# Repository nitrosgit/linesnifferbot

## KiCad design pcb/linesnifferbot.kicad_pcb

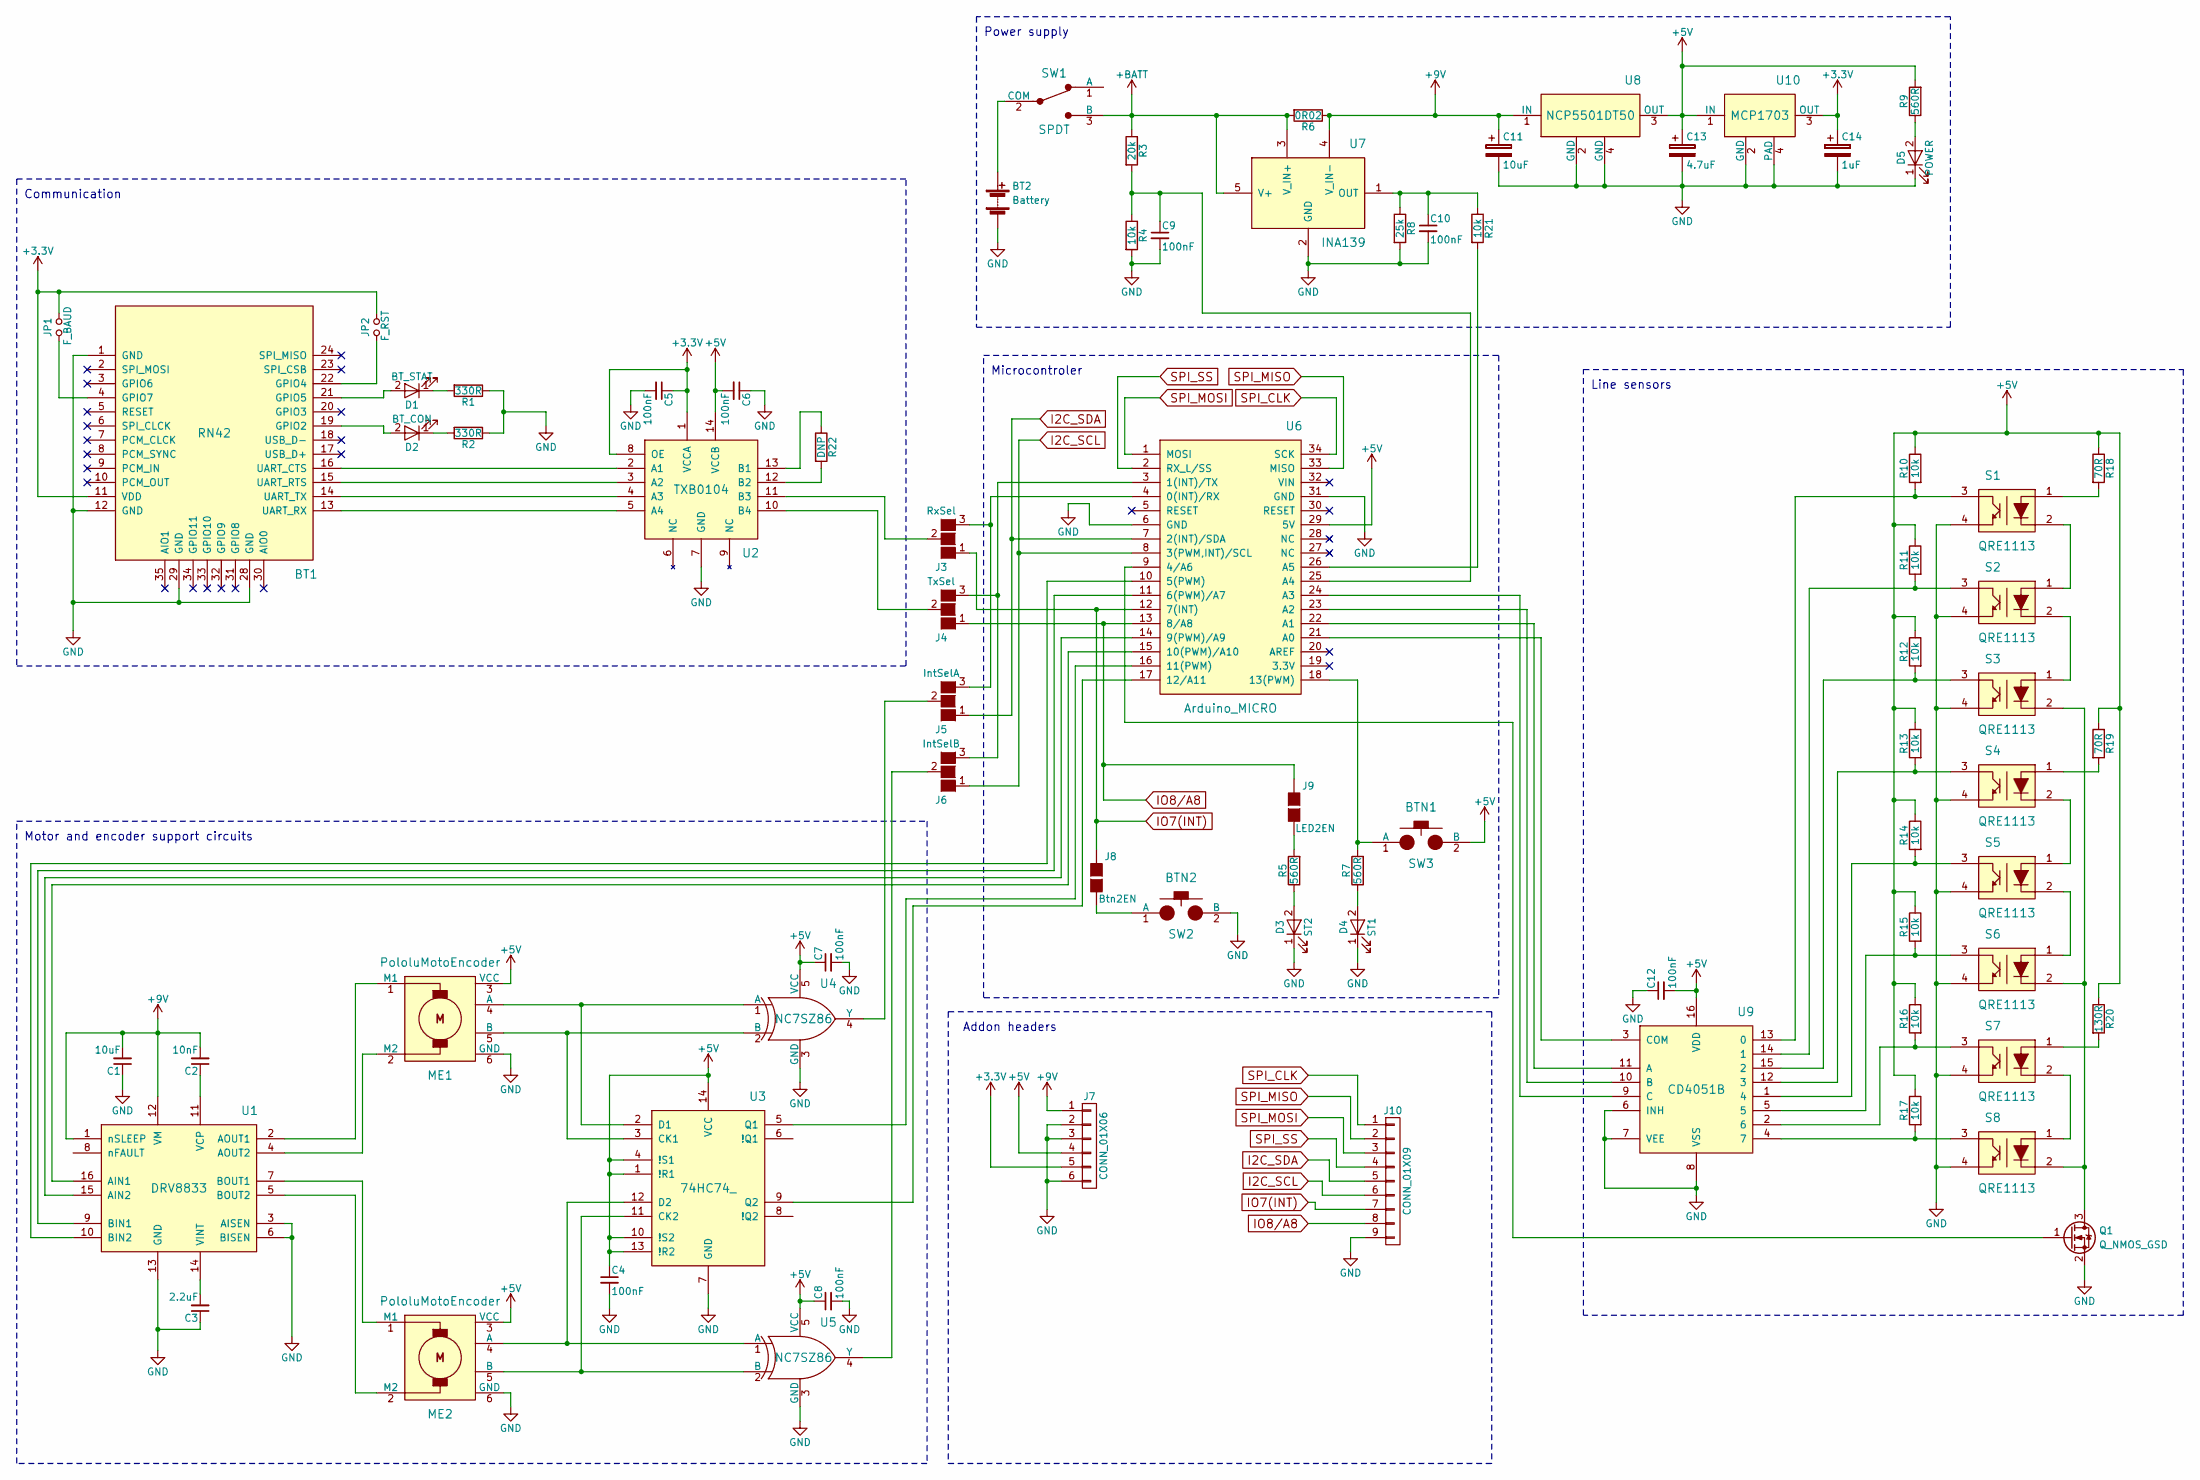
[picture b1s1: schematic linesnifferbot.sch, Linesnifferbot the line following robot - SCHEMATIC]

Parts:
BT1: RN42; RN-42
BT2: Battery; PP3Battery
C1: 10uF; C_1206
C2: 10nF; C_0805
C3: 2.2uF; C_0805
C4, C5, C6, C7, C8, C9, C10, C12: 100nF; C_0805
C11: 10uF; CP_Tantalum_Case-A_EIA-3216-18_Reflow
C13: 4.7uF; CP_Tantalum_Case-A_EIA-3216-18_Reflow
C14: 1uF; CP_Tantalum_Case-A_EIA-3216-18_Reflow
D1: BT_STAT; LED_0805
D2: BT_CON; LED_0805
D3: ST2; LED_0805
D4: ST1; LED_0805
D5: POWER; LED_0805
J3: RxSel; GS3
J4: TxSel; GS3
J5: IntSelA; GS3
J6: IntSelB; GS3
J7: CONN_01X06; Socket_Strip_Straight_1x06_Pitch2.54mm
J8: Btn2EN; GS2
J9: LED2EN; GS2
J10: CONN_01X09; Socket_Strip_Straight_1x09_Pitch2.54mm
JP1: F_BAUD; GS2
JP2: F_RST; GS2
ME1, ME2: PololuMotoEncoder
Q1: Q_NMOS_GSD; SOT-23
R1, R2: 330R; R_0805
R3: 20k; R_0805
R4, R10, R11, R12, R13, R14, R15, R16, R17, R21: 10k; R_0805
R5, R7, R9: 560R; R_0805
R6: 0R02; R_1206
R8: 25k; R_0805
R18, R19: 70R; R_0805
R20: 130R; R_0805
R22: DNP; R_0805
S1, S2, S3, S4, S5, S6, S7, S8: QRE1113; QRE1113GR
SW1: SPDT; SP_ToggleSW
SW2: BTN2; SW_SPST_EVPBF
SW3: BTN1; SW_SPST_EVPBF
U1: DRV8833; TSSOP-16_4.4x5mm_Pitch0.65mm
U2: TXB0104; SOIC-14_3.9x8.7mm_Pitch1.27mm
U3: 74HC74_; SOIC-14_3.9x8.7mm_Pitch1.27mm
U4, U5: NC7SZ86; SOT-23-5
U6: Arduino_MICRO; ArduinoMicro
U7: INA139; SOT-23-5
U8: NCP5501DT50; DPAK3
U9: CD4051B; SOIC-16_3.9x9.9mm_Pitch1.27mm
U10: MCP1703; SOT-223

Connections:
+3V3: BT1.11 (VDD), C5.1, C14.1, J7.5, JP1.2, JP2.2, U2.1 (VCCA), U2.8 (OE), U10.3 (OUT)
+5V: C4.1, C6.2, C7.1, C8.1, C12.2, C13.1, J7.4, ME1.3 (VCC), ME2.3 (VCC), R9.2, R10.1, R11.1, R12.1, R13.1, R14.1, R15.1, R16.1, R17.1, R18.1, R19.1, R20.1, SW3.2 (B), U2.14 (VCCB), U3.1 (!R1), U3.4 (!S1), U3.10 (!S2), U3.13 (!R2), U3.14 (VCC), U4.5 (VCC), U5.5 (VCC), U6.29 (5V), U8.3 (OUT), U9.16 (VDD), U10.1 (IN)
+9V: C1.2, C2.2, C11.1, J7.1, R6.1, U1.1 (nSLEEP), U1.12 (VM), U7.4 (V_IN-), U8.1 (IN)
+BATT: R3.1, R6.2, SW1.3 (B), U7.3 (V_IN+), U7.5 (V+)
GND: BT1.1 (GND), BT1.12 (GND), BT1.28 (GND), BT1.29 (GND), BT2.2 (-), C1.1, C3.1, C4.2, C5.2, C6.1, C7.2, C8.2, C9.2, C10.2, C11.2, C12.1, C13.2, C14.2, D3.1 (K), D4.1 (K), D5.1 (K), J7.2, J7.3, J7.6, J10.9, ME1.6 (GND), ME2.6 (GND), Q1.2 (S), R1.1, R2.1, R4.2, R8.2, S1.4, S2.4, S3.4, S4.4, S5.4, S6.4, S7.4, S8.4, SW2.2 (B), U1.3 (AISEN), U1.6 (BISEN), U1.13 (GND), U2.7 (GND), U3.7 (GND), U4.3 (GND), U5.3 (GND), U6.6 (GND), U6.31 (GND), U7.2 (GND), U8.2 (GND), U8.4 (GND), U9.6 (INH), U9.7 (VEE), U9.8 (VSS), U10.2 (GND), U10.4 (PAD)
I2C_SCL: J6.1 (G1), J10.6, U6.8 (3(PWM,INT)/SCL)
I2C_SDA: J5.1 (G1), J10.5, U6.7 (2(INT)/SDA)
IO7(INT): J3.1 (G1), J8.1 (G1), J10.7, U6.12 (7(INT))
IO8/A8: J4.1 (G1), J9.1 (G1), J10.8, U6.13 (8/A8)
unnamed: BT1.4 (GPIO7), JP1.1
unnamed: BT1.13 (UART_RX), U2.5 (A4)
unnamed: BT1.14 (UART_TX), U2.4 (A3)
unnamed: BT1.15 (UART_RTS), U2.3 (A2)
unnamed: BT1.16 (UART_CTS), U2.2 (A1)
unnamed: BT1.19 (GPIO2), D2.2 (A)
unnamed: BT1.21 (GPIO5), D1.2 (A)
unnamed: BT1.22 (GPIO4), JP2.1
unnamed: BT2.1 (+), SW1.2 (COM)
unnamed: C2.1, U1.11 (VCP)
unnamed: C3.2, U1.14 (VINT)
unnamed: C9.1, R3.2, R4.1, U6.25 (A4)
unnamed: C10.1, R8.1, R21.1, U7.1 (OUT)
unnamed: D1.1 (K), R1.2
unnamed: D2.1 (K), R2.2
unnamed: D3.2 (A), R5.1
unnamed: D4.2 (A), R7.1
unnamed: D5.2 (A), R9.1
unnamed: J3.2 (G2), U2.11 (B3)
unnamed: J3.3 (G3), J5.3 (G3), U6.4 (0(INT)/RX)
unnamed: J4.2 (G2), U2.10 (B4)
unnamed: J4.3 (G3), J6.3 (G3), U6.3 (1(INT)/TX)
unnamed: J5.2 (G2), U4.4 (Y)
unnamed: J6.2 (G2), U5.4 (Y)
unnamed: J8.2 (G2), SW2.1 (A)
unnamed: J9.2 (G2), R5.2
unnamed: ME1.1 (M1), U1.2 (AOUT1)
unnamed: ME1.2 (M2), U1.4 (AOUT2)
unnamed: ME1.4 (A), U3.2 (D1), U4.1 (A)
unnamed: ME1.5 (B), U3.3 (CK1), U4.2 (B)
unnamed: ME2.1 (M1), U1.7 (BOUT1)
unnamed: ME2.2 (M2), U1.5 (BOUT2)
unnamed: ME2.4 (A), U3.12 (D2), U5.1 (A)
unnamed: ME2.5 (B), U3.11 (CK2), U5.2 (B)
unnamed: Q1.1 (G), U6.9 (4/A6)
unnamed: Q1.3 (D), S3.2, S6.2, S8.2
unnamed: R7.2, SW3.1 (A), U6.18 (13(PWM))
unnamed: R10.2, S1.3, U9.13 (0)
unnamed: R11.2, S2.3, U9.14 (1)
unnamed: R12.2, S3.3, U9.15 (2)
unnamed: R13.2, S4.3, U9.12 (3)
unnamed: R14.2, S5.3, U9.1 (4)
unnamed: R15.2, S6.3, U9.5
unnamed: R16.2, S7.3, U9.2 (6)
unnamed: R17.2, S8.3, U9.4 (7)
unnamed: R18.2, S1.1
unnamed: R19.2, S4.1
unnamed: R20.2, S7.1
unnamed: R21.2, U6.26 (A5)
unnamed: R22.1, U2.13 (B1)
unnamed: R22.2, U2.12 (B2)
unnamed: S1.2, S2.1
unnamed: S2.2, S3.1
unnamed: S4.2, S5.1
unnamed: S5.2, S6.1
unnamed: S7.2, S8.1
unnamed: U1.9 (BIN1), U6.11 (6(PWM)/A7)
unnamed: U1.10 (BIN2), U6.10 (5(PWM))
unnamed: U1.15 (AIN2), U6.14 (9(PWM)/A9)
unnamed: U1.16 (AIN1), U6.15 (10(PWM)/A10)
unnamed: U3.5 (Q1), U6.16 (11(PWM))
unnamed: U3.9 (Q2), U6.17 (12/A11)
unnamed: U6.21 (A0), U9.3 (COM)
unnamed: U6.22 (A1), U9.11 (A)
unnamed: U6.23 (A2), U9.10 (B)
unnamed: U6.24 (A3), U9.9 (C)
SPI_CLK: J10.1, U6.34 (SCK)
SPI_MISO: J10.2, U6.33 (MISO)
SPI_MOSI: J10.3, U6.1 (MOSI)
SPI_SS: J10.4, U6.2 (RX_L/SS)

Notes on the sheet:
Motor and encoder support circuits
Communication
Line sensors
Power supply
Addon headers
Microcontroler

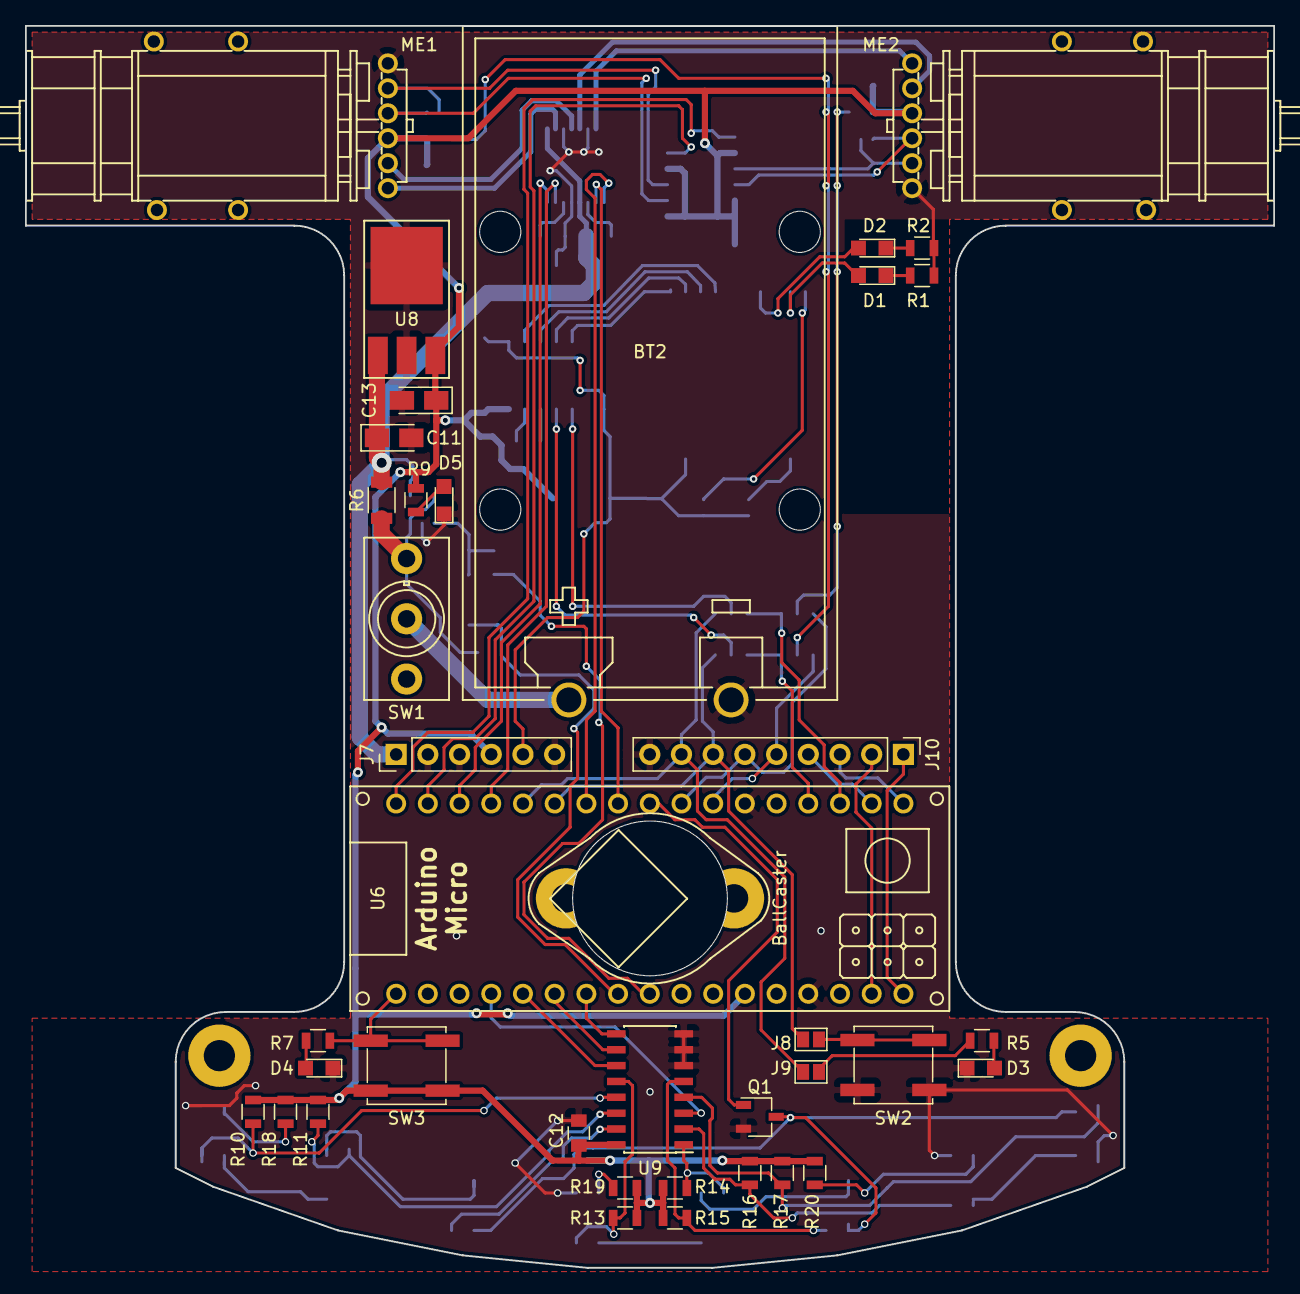
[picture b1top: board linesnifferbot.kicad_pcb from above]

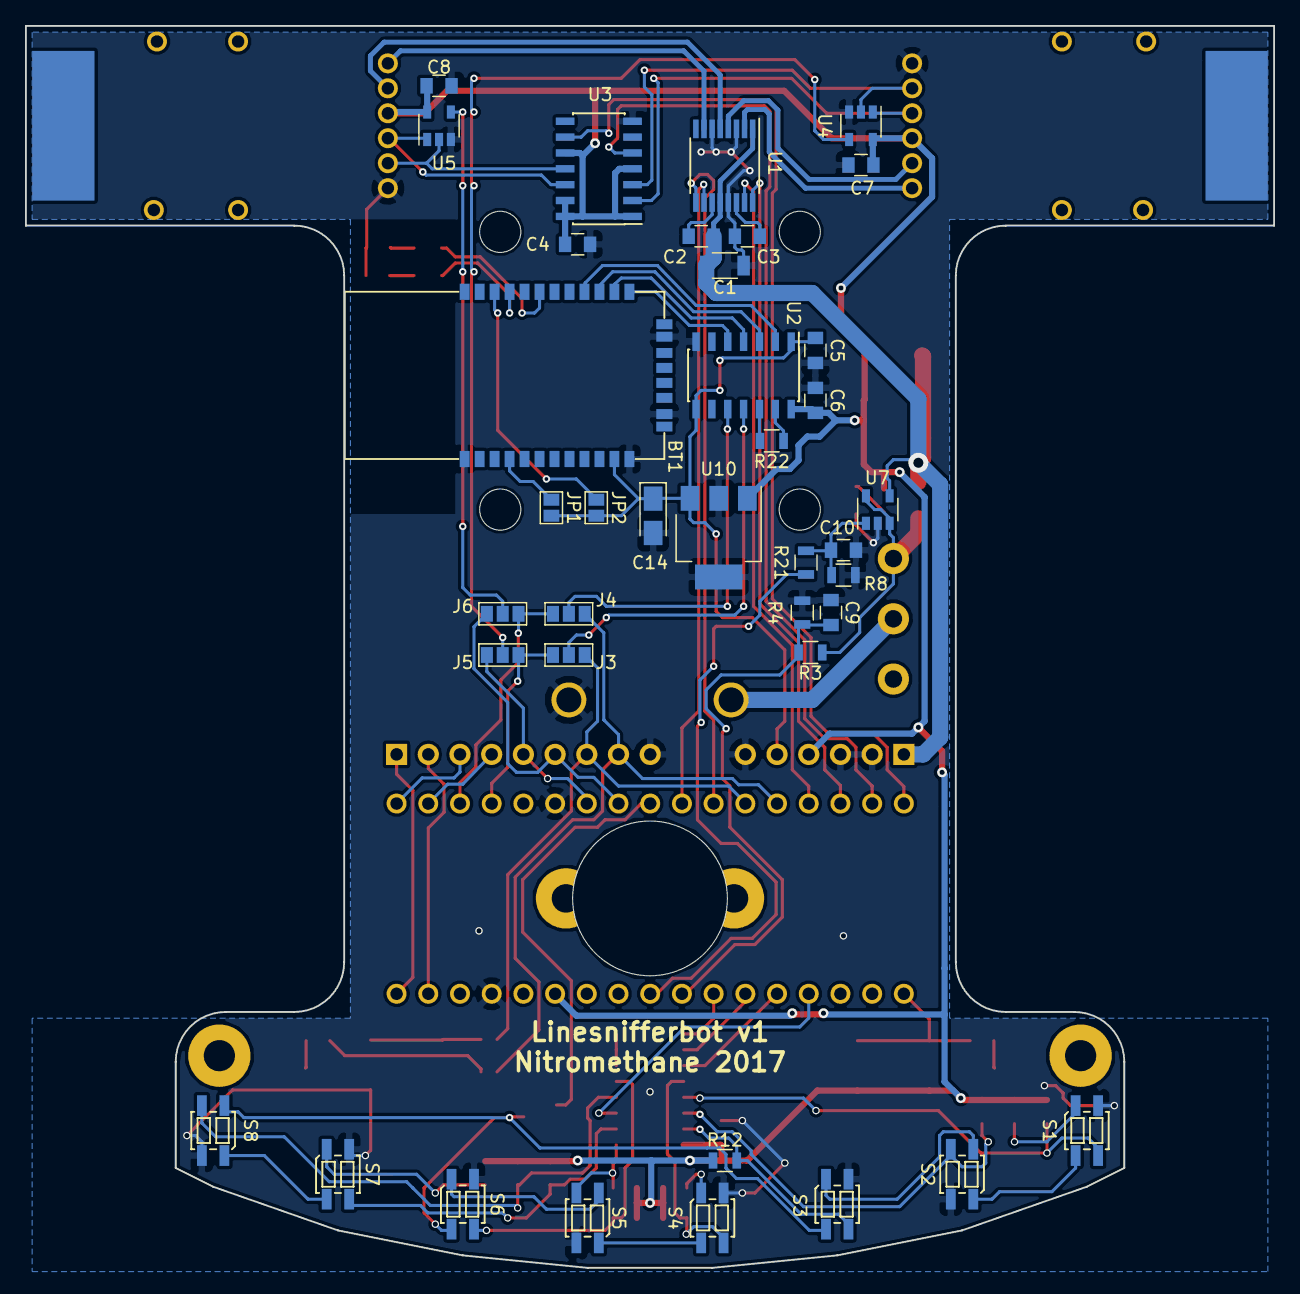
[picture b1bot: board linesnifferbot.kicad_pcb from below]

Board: 2 copper layers, 100.0 x 99.5 mm, 78 parts (39 on the bottom side), 79 nets.

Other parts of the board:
BallCaster: PololuBallCaster_3-8in

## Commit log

2017-02-27 Firs blod
2017-03-05 2. commit
2017-03-05 Created some new library files and started work on schematic
2017-03-05 minor clean up
2017-03-06 Moving along...
2017-03-13 Updated schematic, geting closer to final form
2017-03-13 Schematic: Additional LED and button
2017-03-26 More or less finalized schematic and First version of PCB
2017-04-02 Moved optical sensors closer together, and some other minor edits to the board
2017-04-03 Added the BallCaster footprint to the PCB
